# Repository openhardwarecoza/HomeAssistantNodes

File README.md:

# HomeAssistantNodes
Various ESP based Home Assistant Nodes

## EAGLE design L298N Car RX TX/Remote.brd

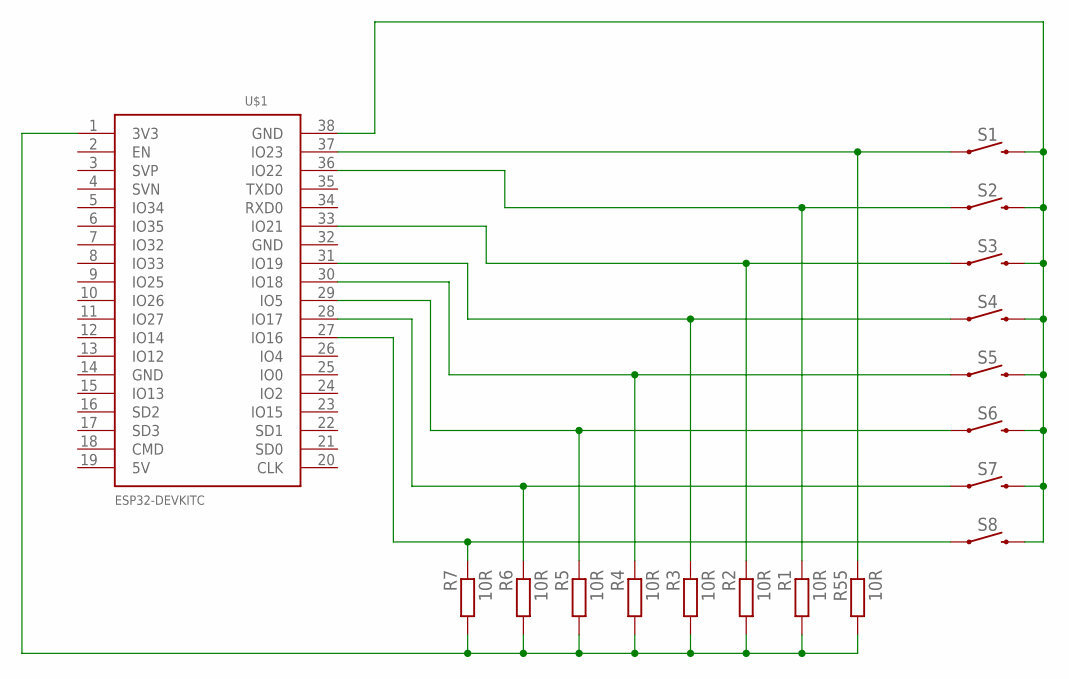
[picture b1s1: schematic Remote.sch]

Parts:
R1, R2, R3, R4, R5, R6, R7, R55: 10R; 0204/7
S1, S2, S3, S4, S5, S6, S7, S8: MOMENTARY-SWITCH-SPST-PTH-12MM; TACTILE_SWITCH_PTH_12MM
U$1: ESP32NODEMCU

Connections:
unnamed: R55.1, S1.1, U$1.37 (IO23)
unnamed: R1.1, S2.1, U$1.36 (IO22)
unnamed: R2.1, S3.1, U$1.33 (IO21)
unnamed: R3.1, S4.1, U$1.31 (IO19)
unnamed: R4.1, S5.1, U$1.30 (IO18)
unnamed: R5.1, S6.1, U$1.29 (IO5)
unnamed: R6.1, S7.1, U$1.28 (IO17)
unnamed: R1.2, R2.2, R3.2, R4.2, R5.2, R6.2, R7.2, R55.2, U$1.1 (3V3)
unnamed: S1.3 (2), S2.3 (2), S3.3 (2), S4.3 (2), S5.3 (2), S6.3 (2), S7.3 (2), S8.3 (2), U$1.38 (GND)
unnamed: R7.1, S8.1, U$1.27 (IO16)

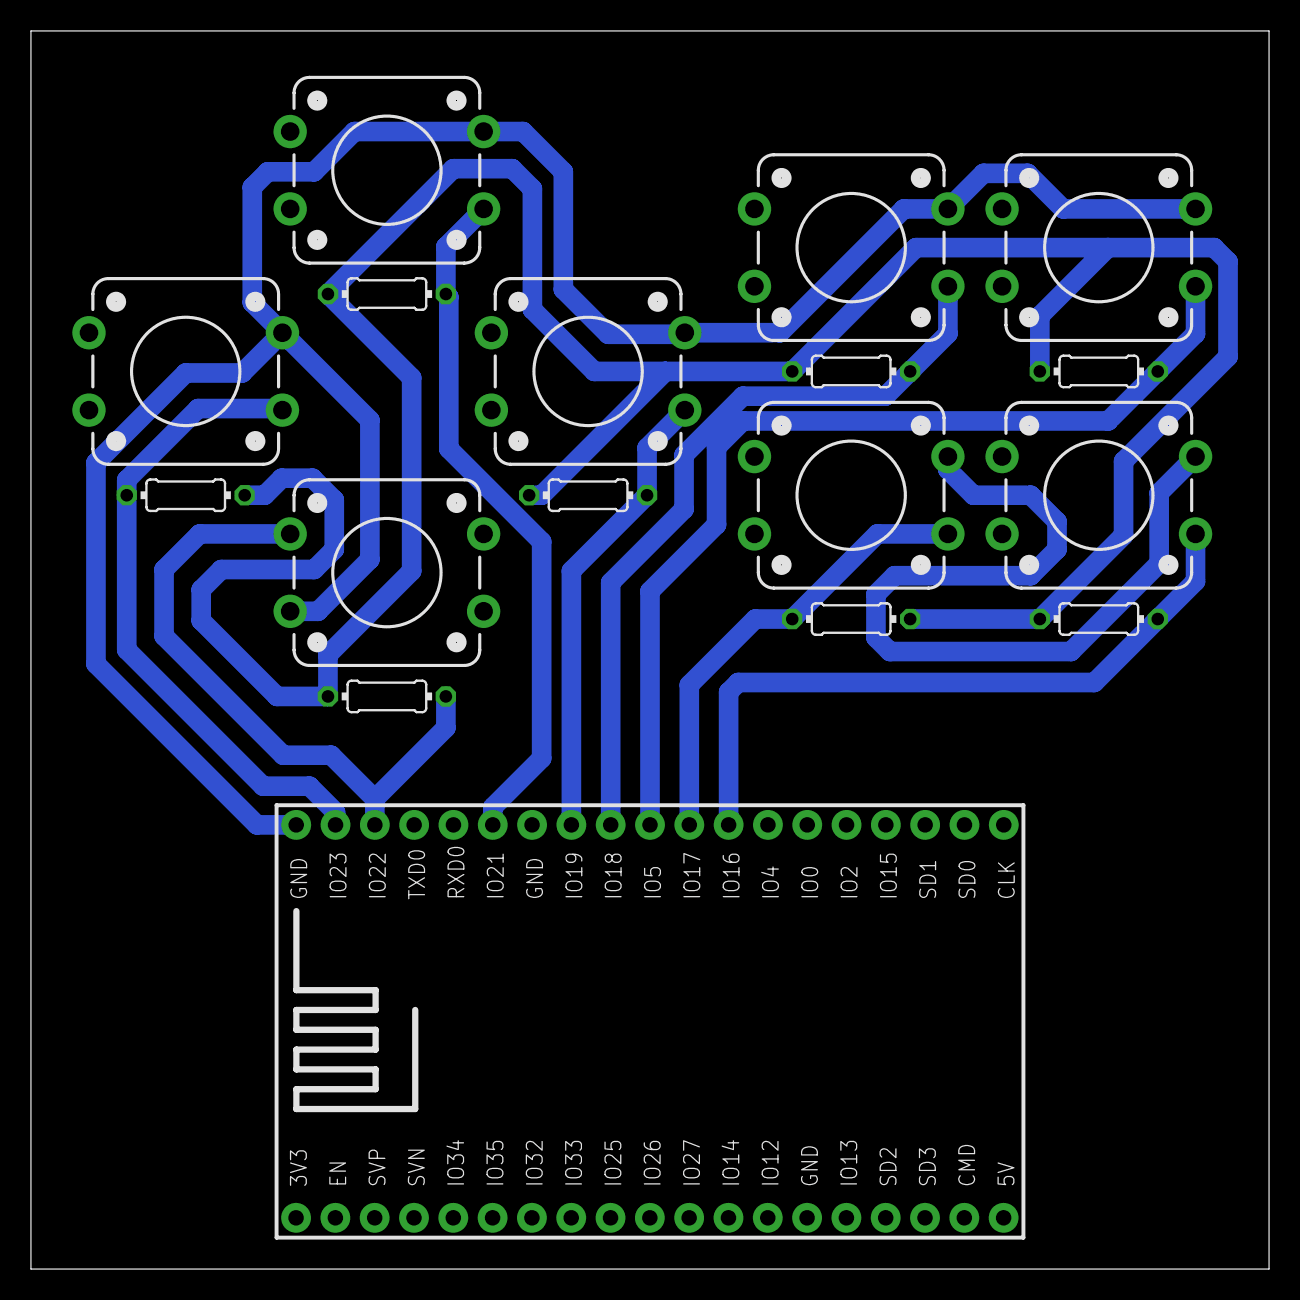
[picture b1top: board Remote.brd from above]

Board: 2 copper layers, 80.0 x 80.0 mm, 17 parts (0 on the bottom side), 10 nets.

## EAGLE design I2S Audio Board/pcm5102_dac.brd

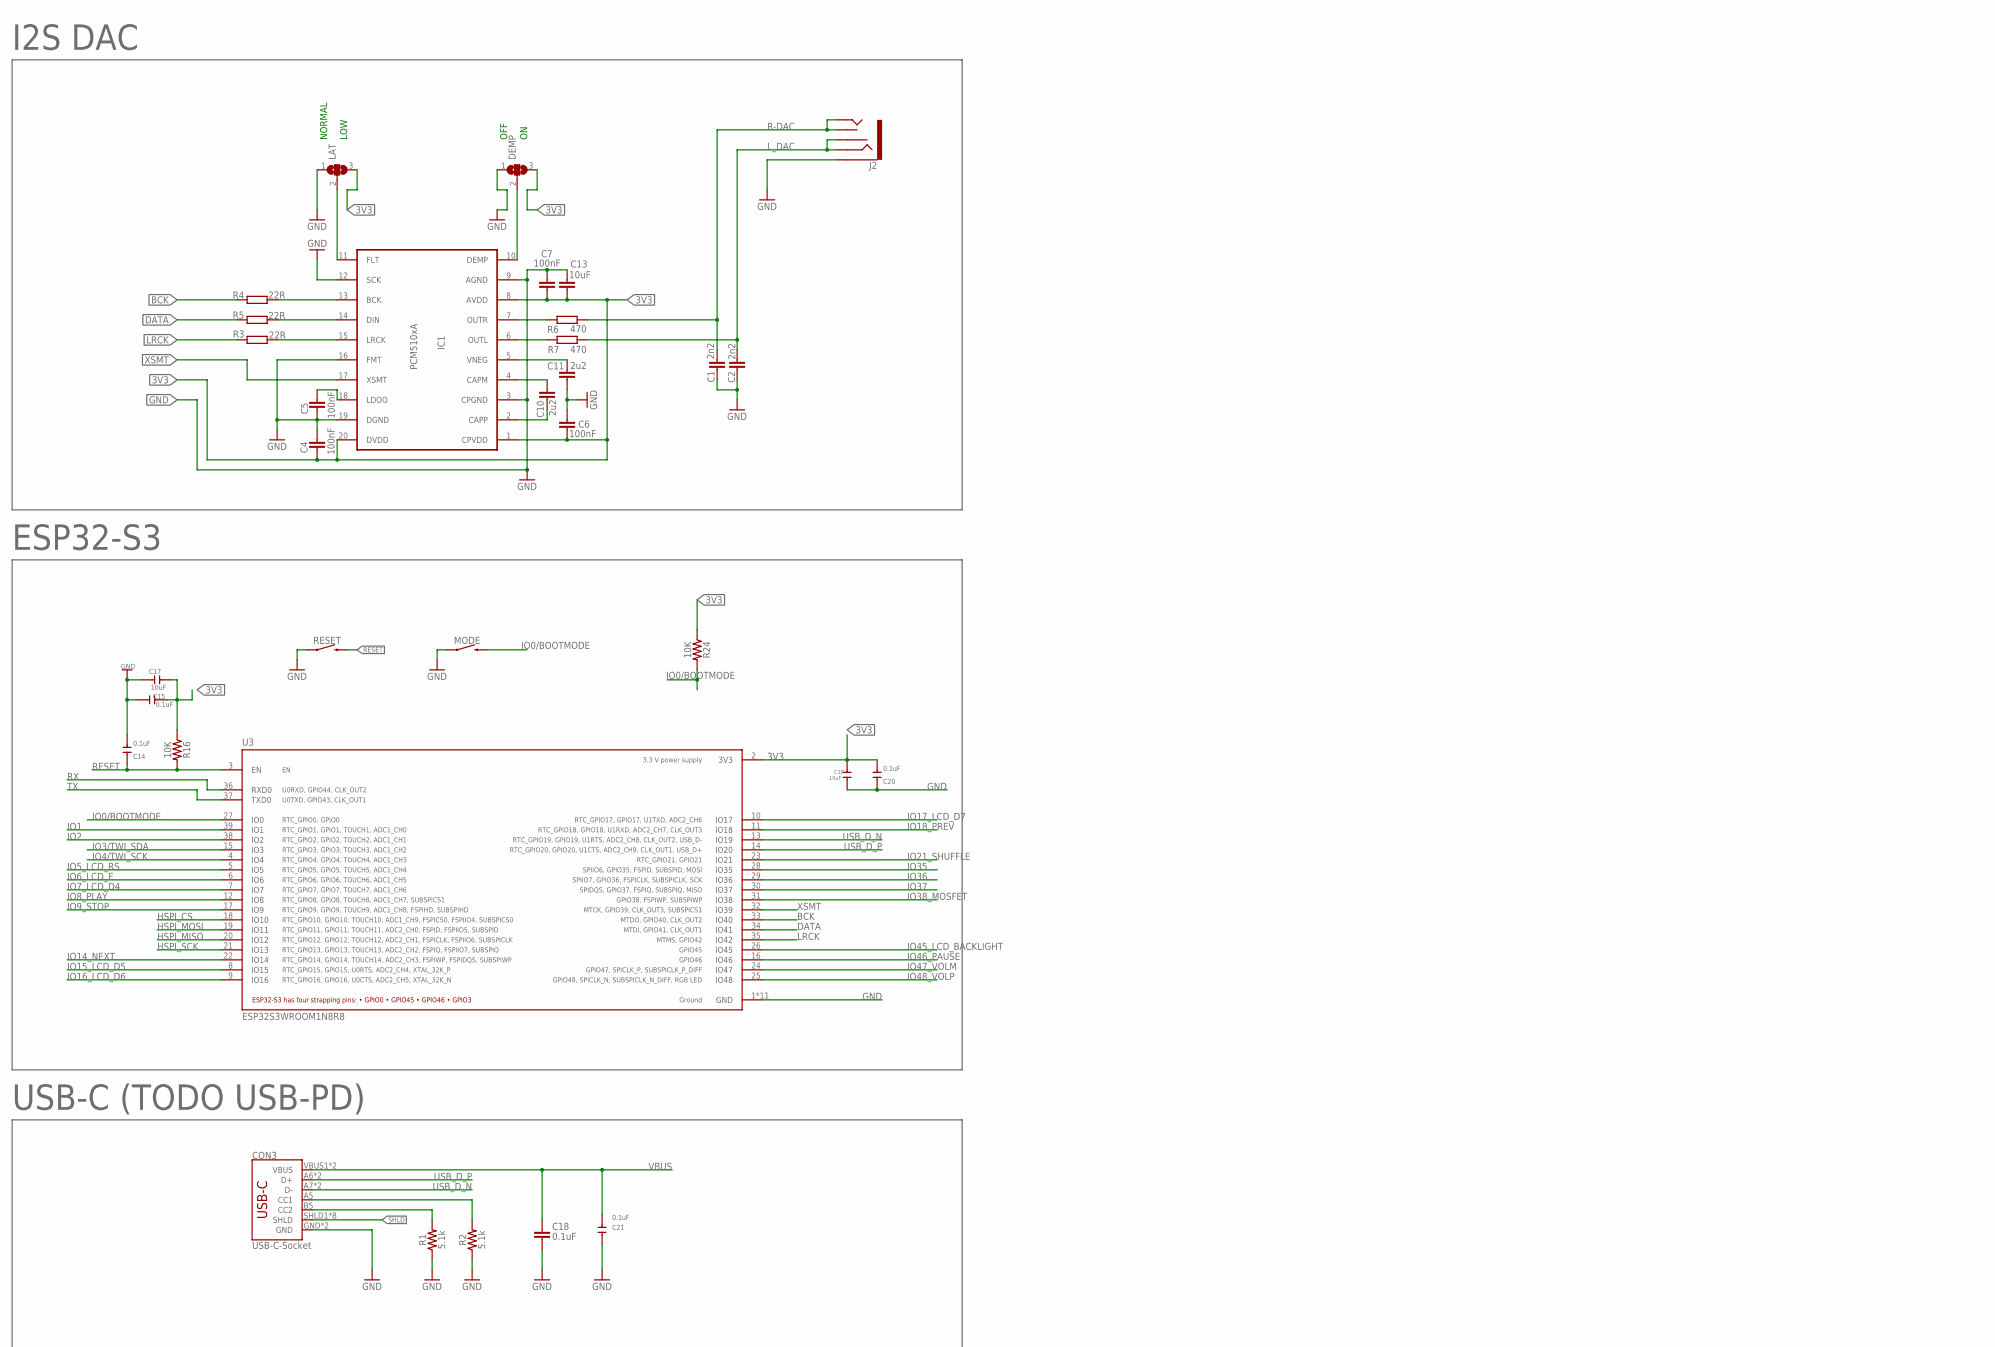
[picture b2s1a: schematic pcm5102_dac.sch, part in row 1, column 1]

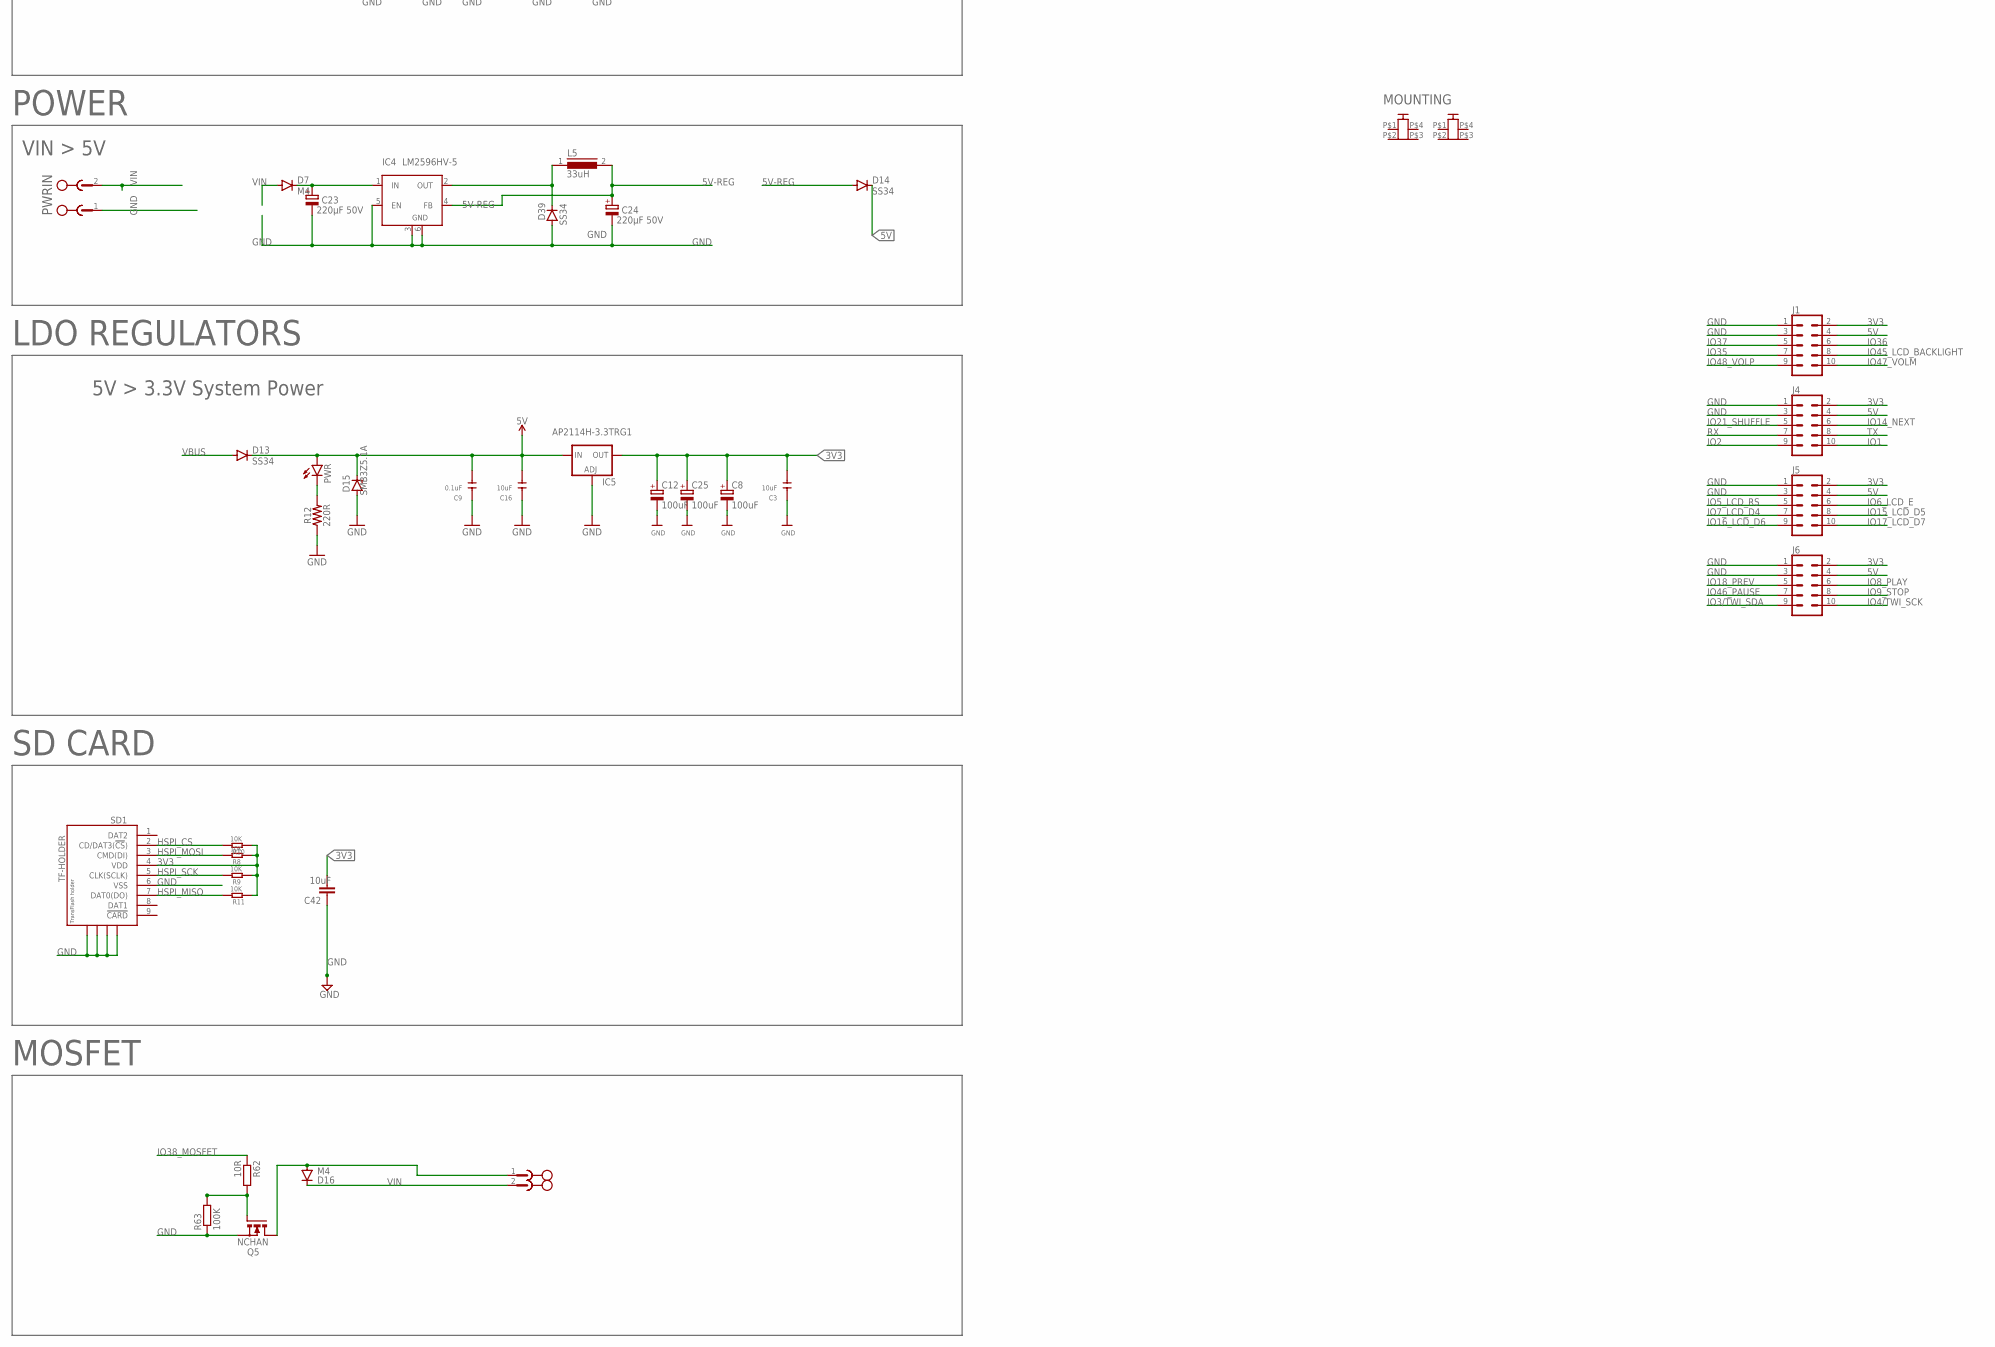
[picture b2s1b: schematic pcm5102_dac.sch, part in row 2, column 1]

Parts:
C1, C2: 2n2; C1206
C3, C17: 10uF; DISCRETE_C1206
C4, C5, C6, C7: 100nF; C1206
C8, C12, C25: 100uF; PANASONIC_D
C9, C14, C15, C20, C21: 0.1uF; DISCRETE_C0603
C10, C11: 2u2; C1206
C13, C16, C19, C42: 10uF; C1206
C18: 0.1uF; 0603-CAP
C23, C24: 220µF 50V; PANASONIC_E
CON3: USB-C-Socket; USB-C-16P
CON7, CON8: PCB-2M3; PCB2-M3
D7, D16: M4; DO-214AC
D13, D14: SS34; DO-214AC
D15: SMB3Z5.1A; SMB
D39: SS34; SOD87
DEMP: SJ2W; SJ_2
IC1: PCM510xA; TSSOP20
IC4: LM2596HV-5; TO263-5
IC5: AP2114H-3.3TRG1; SOT223
J1, J4, J5, J6: CONN_05X2SHD; 2X5-SHROUDED
J2: AUDIO_JACK_3.5MM_PTH; AUDIO-JACK
L5: 33uH; DR127
LAT: SJ2W; SJ_2
MODE: MOMENTARY-SWITCH-SPST-PTH-6.0MM; TACTILE_SWITCH_PTH_6.0MM
PWR: LED3MM
PWRIN: Phoenix Pluggable 5.08mm 2 way; MSTBA2
Q5: NCHAN; D-PAK_TO252AA
R1, R2: 5.1k; 0603@1
R3, R4, R5: 22R; R0805
R6, R7: 470; R1206
R8, R9, R10, R11: 10K; R0603
R12: 220R; 0603@1
R16, R24: 10K; 0603@1
R62: 10R; R0603
R63: 100K; R0603
RESET: MOMENTARY-SWITCH-SPST-PTH-6.0MM; TACTILE_SWITCH_PTH_6.0MM
SD1: TF-HOLDER; TF-PULL
SWOUT: Phoenix Pluggable 5.08mm 2 way; MSTBA2
U3: ESP32S3WROOM1N8R8; XCVR_ESP32S3WROOM1N8R8

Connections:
3V3: C3.2, C4.2, C6.2, C7.2, C8.+, C12.+, C13.2, C15.1, C17.1, C19.1, C20.2, C25.+, C42.2, DEMP.3, IC1.1 (CPVDD), IC1.8 (AVDD), IC1.20 (DVDD), IC5.4 (OUT), J1.2, J4.2, J5.2, J6.2, LAT.3, R8.1, R9.1, R10.1, R11.1, R16.1, R24.1, SD1.4 (VDD), U3.2 (3V3)
5V: C9.2, C16.1, D13.C, D14.C, D15.C, IC5.3 (IN), J1.4, J4.4, J5.4, J6.4, PWR.A
5V-REG: C24.+, D14.A, IC4.4 (FB), L5.2
+24V: C23.+, D7.C, IC4.1 (IN)
BCK: R4.1, U3.33 (IO40)
CC1: CON3.A5 (CC1), R2.2
CC2: CON3.B5 (CC2), R1.2
DATA: R5.1, U3.34 (IO41)
GND: C1.2, C2.2, C3.1, C4.1, C5.2, C6.1, C7.1, C8.-, C9.1, C11.2, C12.-, C13.1, C14.2, C15.2, C16.2, C17.2, C18.2, C19.2, C20.1, C21.1, C23.-, C24.-, C25.-, C42.1, CON3.GND, CON3.GND2 (GND), D15.A, D39.2 (A), DEMP.1, IC1.3 (CPGND), IC1.9 (AGND), IC1.12 (SCK), IC1.16 (FMT), IC1.19 (DGND), IC4.3 (GND), IC4.5 (EN), IC4.6 (GND), IC5.1 (ADJ), J1.1, J1.3, J2.SLEEVE, J4.1, J4.3, J5.1, J5.3, J6.1, J6.3, LAT.1, MODE.1, PWRIN.1, Q5.3 (S), R1.1, R2.1, R12.1, R63.1, RESET.1, SD1.6 (VSS), SD1.S1, SD1.S2, SD1.S3, SD1.S4, U3.1 (GND), U3.40 (GND), U3.41_1 (GND), U3.41_2 (GND), U3.41_3 (GND), U3.41_4 (GND), U3.41_5 (GND), U3.41_6 (GND), U3.41_7 (GND), U3.41_8 (GND), U3.41_9 (GND)
HSPI_CS: R10.2, SD1.2 (CD/DAT3(!CS!)), U3.18 (IO10)
HSPI_MISO: R11.2, SD1.7 (DAT0(DO)), U3.20 (IO12)
HSPI_MOSI: R8.2, SD1.3 (CMD(DI)), U3.19 (IO11)
HSPI_SCK: R9.2, SD1.5 (CLK(SCLK)), U3.21 (IO13)
IO0/BOOTMODE: MODE.3 (2), R24.2, U3.27 (IO0)
IO1: J4.10, U3.39 (IO1)
IO2: J4.9, U3.38 (IO2)
IO3/TWI_SDA: J6.9, U3.15 (IO3)
IO4/TWI_SCK: J6.10, U3.4 (IO4)
IO5_LCD_RS: J5.5, U3.5 (IO5)
IO6_LCD_E: J5.6, U3.6 (IO6)
IO7_LCD_D4: J5.7, U3.7 (IO7)
IO8_PLAY: J6.6, U3.12 (IO8)
IO9_STOP: J6.8, U3.17 (IO9)
IO14_NEXT: J4.6, U3.22 (IO14)
IO15_LCD_D5: J5.8, U3.8 (IO15)
IO16_LCD_D6: J5.9, U3.9 (IO16)
IO17_LCD_D7: J5.10, U3.10 (IO17)
IO18_PREV: J6.5, U3.11 (IO18)
IO21_SHUFFLE: J4.5, U3.23 (IO21)
IO35: J1.7, U3.28 (IO35)
IO36: J1.6, U3.29 (IO36)
IO37: J1.5, U3.30 (IO37)
IO38_MOSFET: R62.1, U3.31 (IO38)
IO45_LCD_BACKLIGHT: J1.8, U3.26 (IO45)
IO46_PAUSE: J6.7, U3.16 (IO46)
IO47_VOLM: J1.10, U3.24 (IO47)
IO48_VOLP: J1.9, U3.25 (IO48)
LDOO: C5.1, IC1.18 (LDOO)
LRCK: R3.1, U3.35 (IO42)
L_DAC: C2.1, J2.RING, J2.RSH, R7.2
MOSFET-GND: D16.A, Q5.4 (D), SWOUT.1
unnamed: PWR.K (C), R12.2
unnamed: Q5.1 (G), R62.2, R63.2
unnamed: IC1.13 (BCK), R4.2
unnamed: IC1.14 (DIN), R5.2
unnamed: IC1.11 (FLT), LAT.2
unnamed: DEMP.2, IC1.10 (DEMP)
unnamed: IC1.15 (LRCK), R3.2
unnamed: C10.1, IC1.4 (CAPM)
unnamed: C10.2, IC1.2 (CAPP)
unnamed: C11.1, IC1.5 (VNEG)
unnamed: IC1.7 (OUTR), R6.1
unnamed: IC1.6 (OUTL), R7.1
unnamed: D39.1 (C), IC4.2 (OUT), L5.1
R-DAC: C1.1, J2.TIP, J2.TSH, R6.2
RESET: C14.1, R16.2, RESET.3 (2), U3.3 (EN)
RX: J4.7, U3.36 (RXD0)
SHLD: CON3.SHLD1 (SHLD), CON3.SHLD2 (SHLD), CON3.SHLD3 (SHLD), CON3.SHLD4 (SHLD), CON3.SHLD5 (SHLD), CON3.SHLD6 (SHLD), CON3.SHLD7 (SHLD), CON3.SHLD8 (SHLD)
TX: J4.8, U3.37 (TXD0)
USB_D_N: CON3.A7 (D-), CON3.B7 (D-), U3.13 (IO19)
USB_D_P: CON3.A6 (D+), CON3.B6 (D+), U3.14 (IO20)
VBUS: C18.1, C21.2, CON3.VBUS1 (VBUS), CON3.VBUS2 (VBUS), D13.A
VIN: D7.A, D16.C, PWRIN.2, SWOUT.2
XSMT: IC1.17 (XSMT), U3.32 (IO39)

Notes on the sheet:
NORMAL
LOW
OFF
POWER
VIN > 5V
ESP32-S3
5V > 3.3V System Power
USB-C (TODO USB-PD)
LDO REGULATORS
PWRIN
MOUNTING
I2S DAC
SD CARD
MOSFET

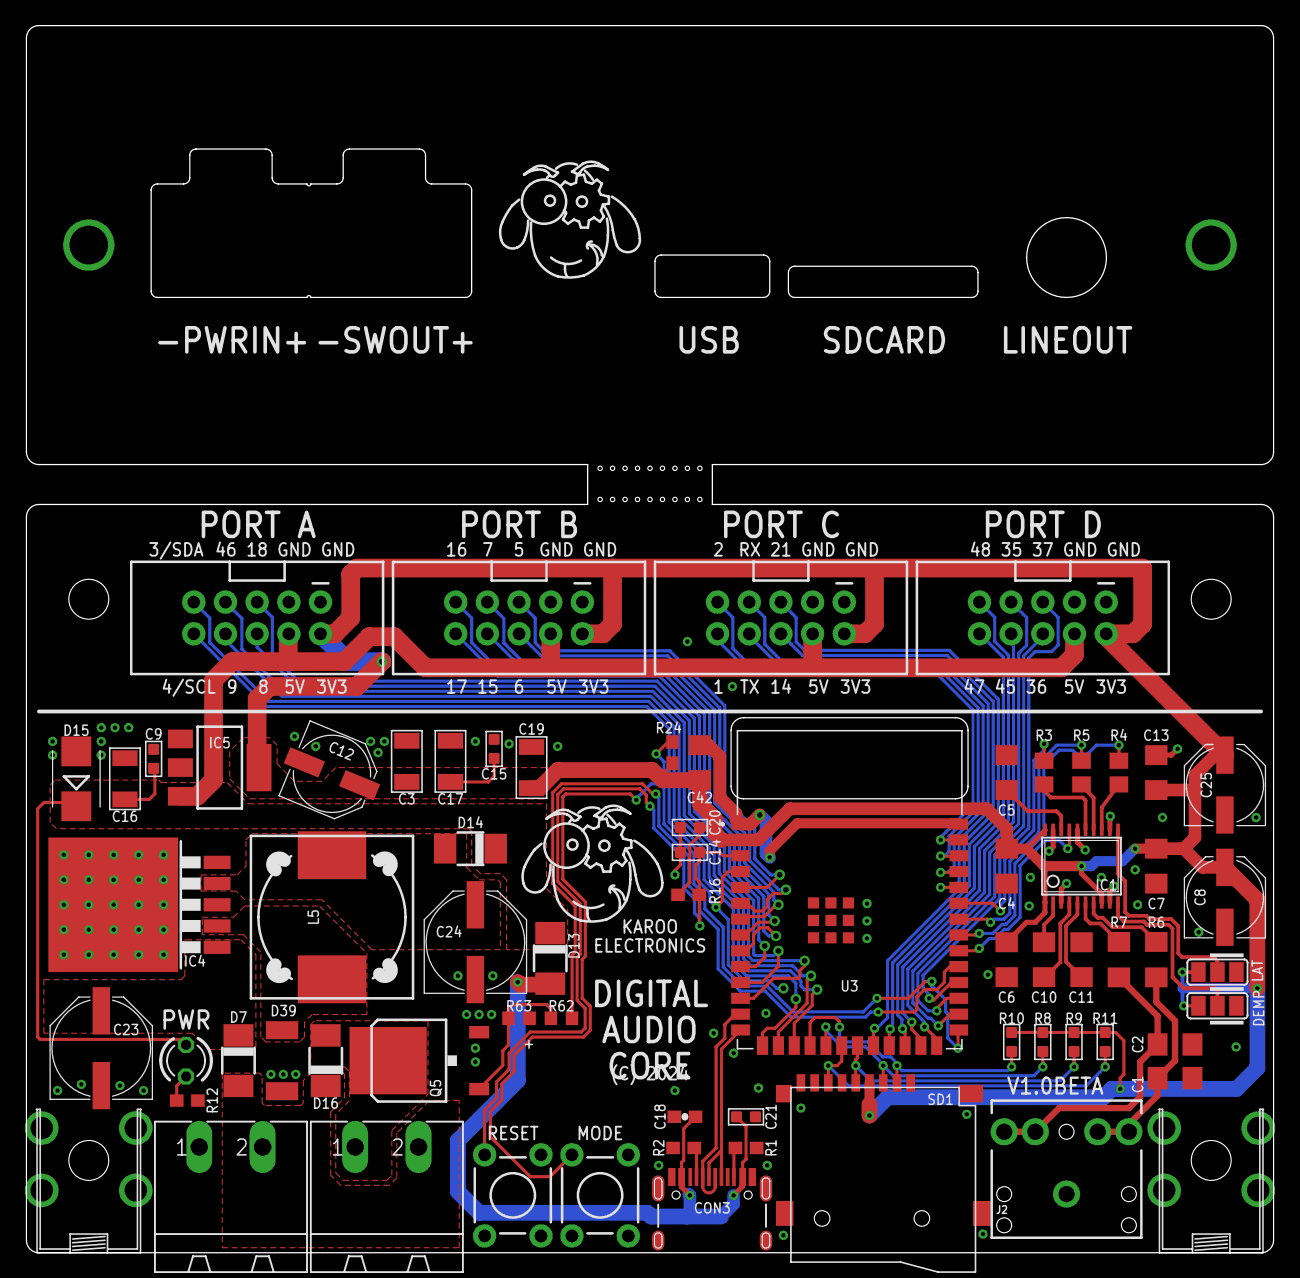
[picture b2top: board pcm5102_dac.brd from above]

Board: 2 copper layers, 100.0 x 98.4 mm, 69 parts (0 on the bottom side), 64 nets.

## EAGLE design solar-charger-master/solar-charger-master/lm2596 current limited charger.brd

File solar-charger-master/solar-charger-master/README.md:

# solar-charger
12v 7AH Switchmode Charger with bells an whistles

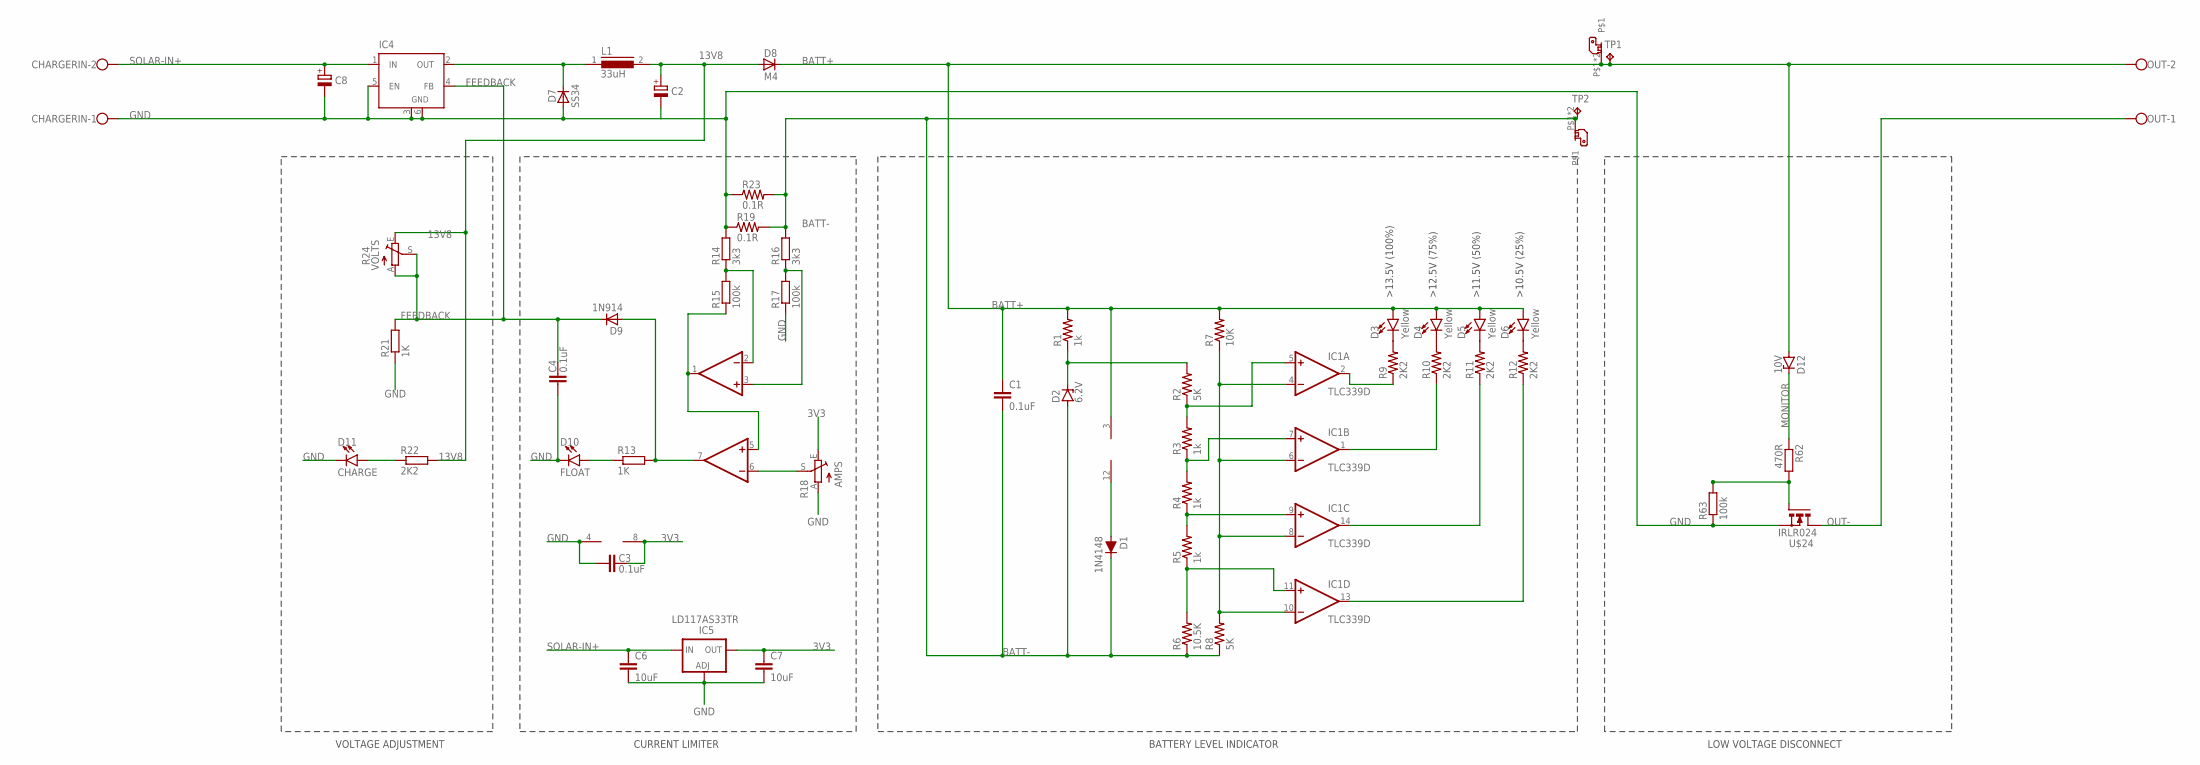
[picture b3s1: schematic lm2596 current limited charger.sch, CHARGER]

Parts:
C1, C3, C4: 0.1uF; C1206K
C2, C8: CPOL-EUE3.5-8; E3,5-8
C6, C7: 10uF; C1206K
CHARGERIN: W237-102
D1: 1N4148; SOD-323
D2: 6.2V; SMB
D3, D4, D5, D6: Yellow; LED-1206
D7: SS34; SOD87
D8: M4; SOD87
D9: 1N914; SOD87
D10: FLOAT; LED-1206
D11: CHARGE; LED-1206
D12: 10V; SMB
IC1: TLC339D; SO14
IC2: MCP602SN; SO08
IC4: LM2596S; TO263-5
IC5: LD117AS33TR; SOT223
L1: 33uH; DR127
OUT: W237-102
R1, R3, R4, R5: 1k; R1206
R2, R8: 5K; R1206
R6: 10.5K; R1206
R7: 10K; R1206
R9, R10, R11, R12, R22: 2K2; R1206
R13, R21: 1K; R1206
R14, R16: 3k3; R1206
R15, R17: 100k; R1206
R18: AMPS; B64Y
R19, R23: 0.1R; R2512
R24: VOLTS; B64Y
R62: 470R; R0603
R63: 100k; R0603
TP1, TP2: TPPAD1-20Y; P1-20Y
U$2, U$3: PCB-6.35MM-RA-SPADE
U$24: IRLR024; D-PAK_TO252AA

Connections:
3V3: C3.2, C7.1, IC2.8 (V+), IC5.4 (OUT), R18.E
13V8: C2.+, D8.2 (A), L1.2, R22.2, R24.E
BATT+: C1.1, D3.A, D4.A, D5.A, D6.A, D8.1 (C), D12.A, IC1.3 (V+), OUT.2, R1.2, R7.2, TP1.TP, U$2.P$1, U$2.P$2
BATT-: C1.2, D1.C, D2.A, R6.1, R8.1, R16.2, R19.2, R23.2, TP2.TP, U$3.P$1, U$3.P$2
FEEDBACK: C4.2, D9.1 (C), IC4.4 (FB), R21.2, R24.A, R24.S
GND: C2.-, C3.1, C4.1, C6.2, C7.2, C8.-, CHARGERIN.1, D7.2 (A), D10.C, D11.C, IC2.4 (V-), IC4.3 (GND), IC4.5 (EN), IC4.6 (GND), IC5.1 (ADJ), R14.2, R17.1, R18.A, R19.1, R21.1, R23.1, R63.1, U$24.3 (S)
MONITOR: D12.C, R62.1
unnamed: D7.1 (C), IC4.2 (OUT), L1.1
unnamed: D2.C, R1.1, R2.2
unnamed: IC1.5 (+IN), R2.1, R3.2
unnamed: IC1.7 (+IN), R3.1, R4.2
unnamed: IC1.9 (+IN), R4.1, R5.2
unnamed: IC1.11 (+IN), R5.1, R6.2
unnamed: IC1.4 (-IN), IC1.6 (-IN), IC1.8 (-IN), IC1.10 (-IN), R7.1, R8.2
unnamed: D3.C, R9.2
unnamed: D4.C, R10.2
unnamed: D5.C, R11.2
unnamed: D6.C, R12.2
unnamed: R62.2, R63.2, U$24.1 (G)
unnamed: IC1.2 (OUT), R9.1
unnamed: IC1.1 (OUT), R10.1
unnamed: IC1.14 (OUT), R11.1
unnamed: IC1.13 (OUT), R12.1
unnamed: D1.A, IC1.12 (V-)
unnamed: D9.2 (A), IC2.7 (OUT), R13.2
unnamed: IC2.6 (-IN), R18.S
unnamed: D10.A, R13.1
unnamed: IC2.1 (OUT), IC2.5 (+IN), R15.1
unnamed: D11.A, R22.1
unnamed: IC2.3 (+IN), R16.1, R17.2
unnamed: IC2.2 (-IN), R14.1, R15.2
OUT-: OUT.1, U$24.4 (D)
SOLAR-IN+: C6.1, C8.+, CHARGERIN.2, IC4.1 (IN), IC5.3 (IN)

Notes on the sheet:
CURRENT LIMITER
VOLTAGE ADJUSTMENT
LOW VOLTAGE DISCONNECT
BATTERY LEVEL INDICATOR

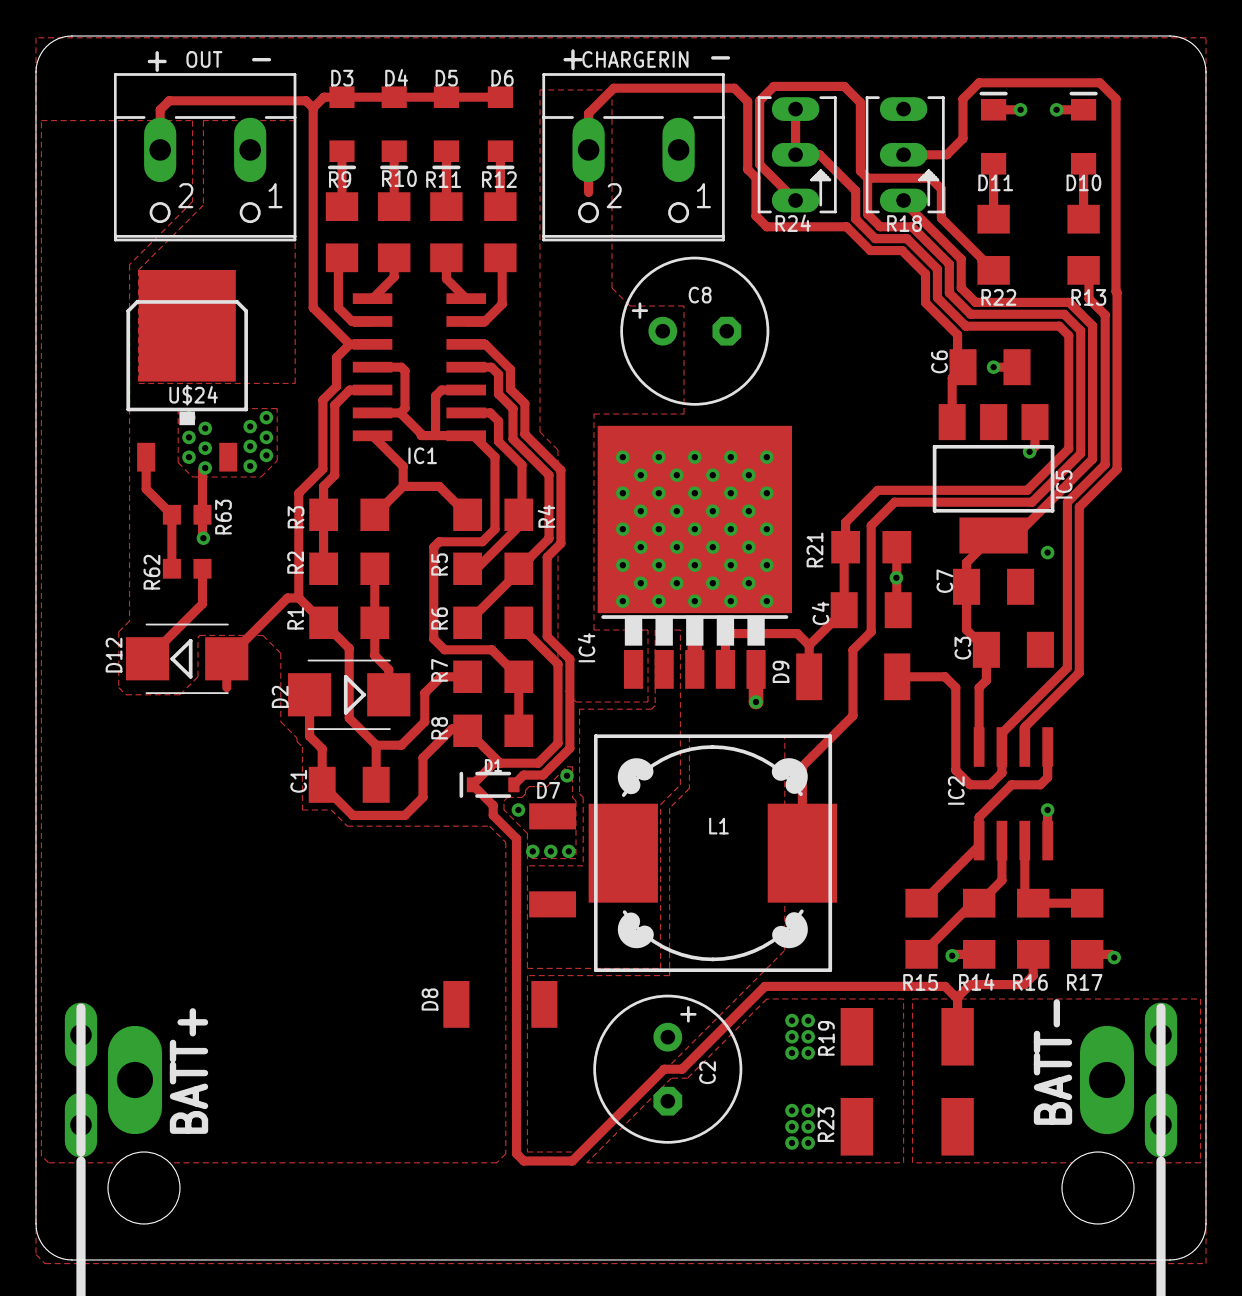
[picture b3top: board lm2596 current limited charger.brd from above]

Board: 2 copper layers, 65.0 x 68.0 mm, 56 parts (0 on the bottom side), 33 nets.

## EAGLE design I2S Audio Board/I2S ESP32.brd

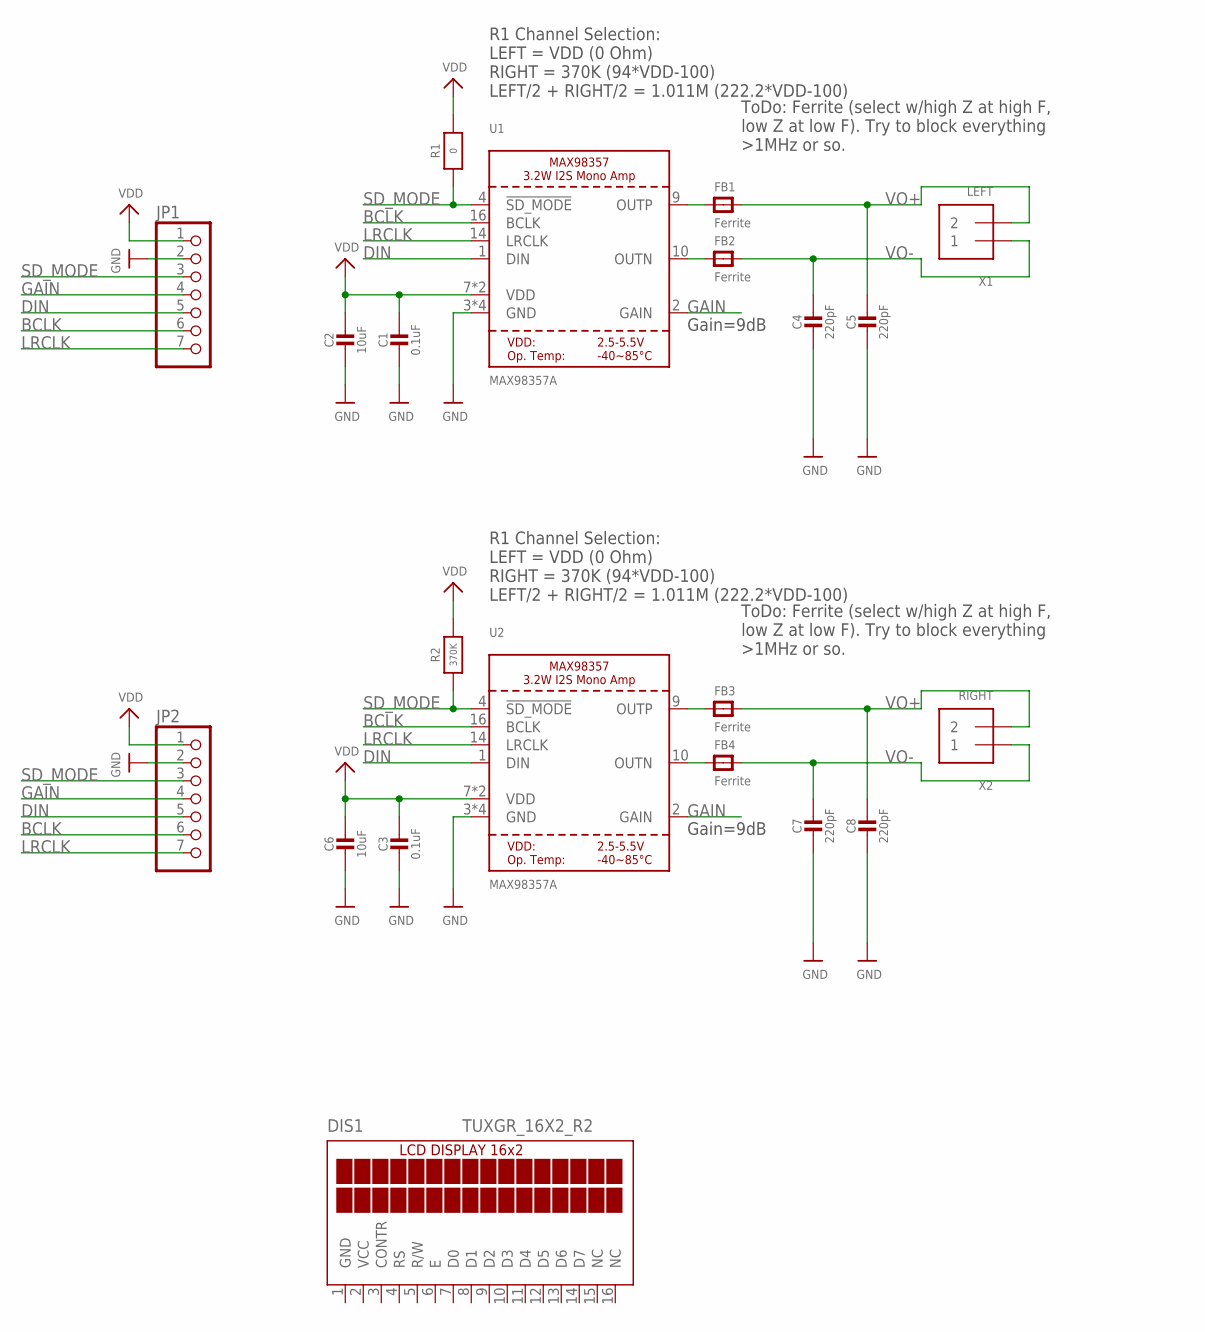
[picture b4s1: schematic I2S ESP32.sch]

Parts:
C1, C3: 0.1uF; 0805-NO
C2, C6: 10uF; 0805-NO
C4, C5, C7, C8: 220pF; 0805-NO
DIS1: TUXGR_16X2_R2
FB1, FB2, FB3, FB4: Ferrite; 0805-NO
JP1, JP2: HEADER-1X7THICKER; 1X07_ROUND_76
R1: 0; 0805-NO
R2: 370K; 0805-NO
U1, U2: MAX98357A; QFN16_3MM
X1: LEFT; TERMBLOCK_1X2-3.5MM
X2: RIGHT; TERMBLOCK_1X2-3.5MM

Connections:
BCLK: JP1.6, JP2.6, U1.16 (BCLK), U2.16 (BCLK)
DIN: JP1.5, JP2.5, U1.1 (DIN), U2.1 (DIN)
GAIN: JP1.4, JP2.4, U1.2 (GAIN), U2.2 (GAIN)
GND: C1.2, C2.2, C3.2, C4.2, C5.2, C6.2, C7.2, C8.2, DIS1.1 (GND), JP1.2, JP2.2, U1.3 (GND), U1.11 (GND), U1.15 (GND), U1.THERMAL (GND), U2.3 (GND), U2.11 (GND), U2.15 (GND), U2.THERMAL (GND)
LRCLK: JP1.7, JP2.7, U1.14 (LRCLK), U2.14 (LRCLK)
unnamed: FB4.1, U2.10 (OUTN)
unnamed: FB3.1, U2.9 (OUTP)
unnamed: FB2.1, U1.10 (OUTN)
unnamed: FB1.1, U1.9 (OUTP)
SD_MODE: JP1.3, JP2.3, R1.1, R2.1, U1.4 (!SD_MODE), U2.4 (!SD_MODE)
VCC: DIS1.2 (VCC)
VDD: C1.1, C2.1, C3.1, C6.1, JP1.1, JP2.1, R1.2, R2.2, U1.7 (VDD), U1.8 (VDD), U2.7 (VDD), U2.8 (VDD)
VO+: C5.1, C8.1, FB1.2, FB3.2, X1.2, X2.2
VO-: C4.1, C7.1, FB2.2, FB4.2, X1.1, X2.1

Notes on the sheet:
R1 Channel Selection: LEFT = VDD (0 Ohm) RIGHT = 370K (94*VDD-100) LEFT/2 + RIGHT/2 = 1.011M (222.2*VDD-100)
ToDo: Ferrite (select w/high Z at high F, low Z at low F). Try to block everything >1MHz or so.
Gain=9dB

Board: 2 copper layers, 21 parts (0 on the bottom side), 13 nets, no tracks yet.

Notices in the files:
I2S Audio Board/pcm5102_dac.brd:
(C) 2024
parts and their libraries:
SparkFun-DiscreteSemi: Licensing: Creative Commons ShareAlike 4.0 International - https://creativecommons.org/licenses/by-sa/4.0
microbuilder: This work is placed in the public domain, and may be freely used for commercial and non-commercial work with the following conditions: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
